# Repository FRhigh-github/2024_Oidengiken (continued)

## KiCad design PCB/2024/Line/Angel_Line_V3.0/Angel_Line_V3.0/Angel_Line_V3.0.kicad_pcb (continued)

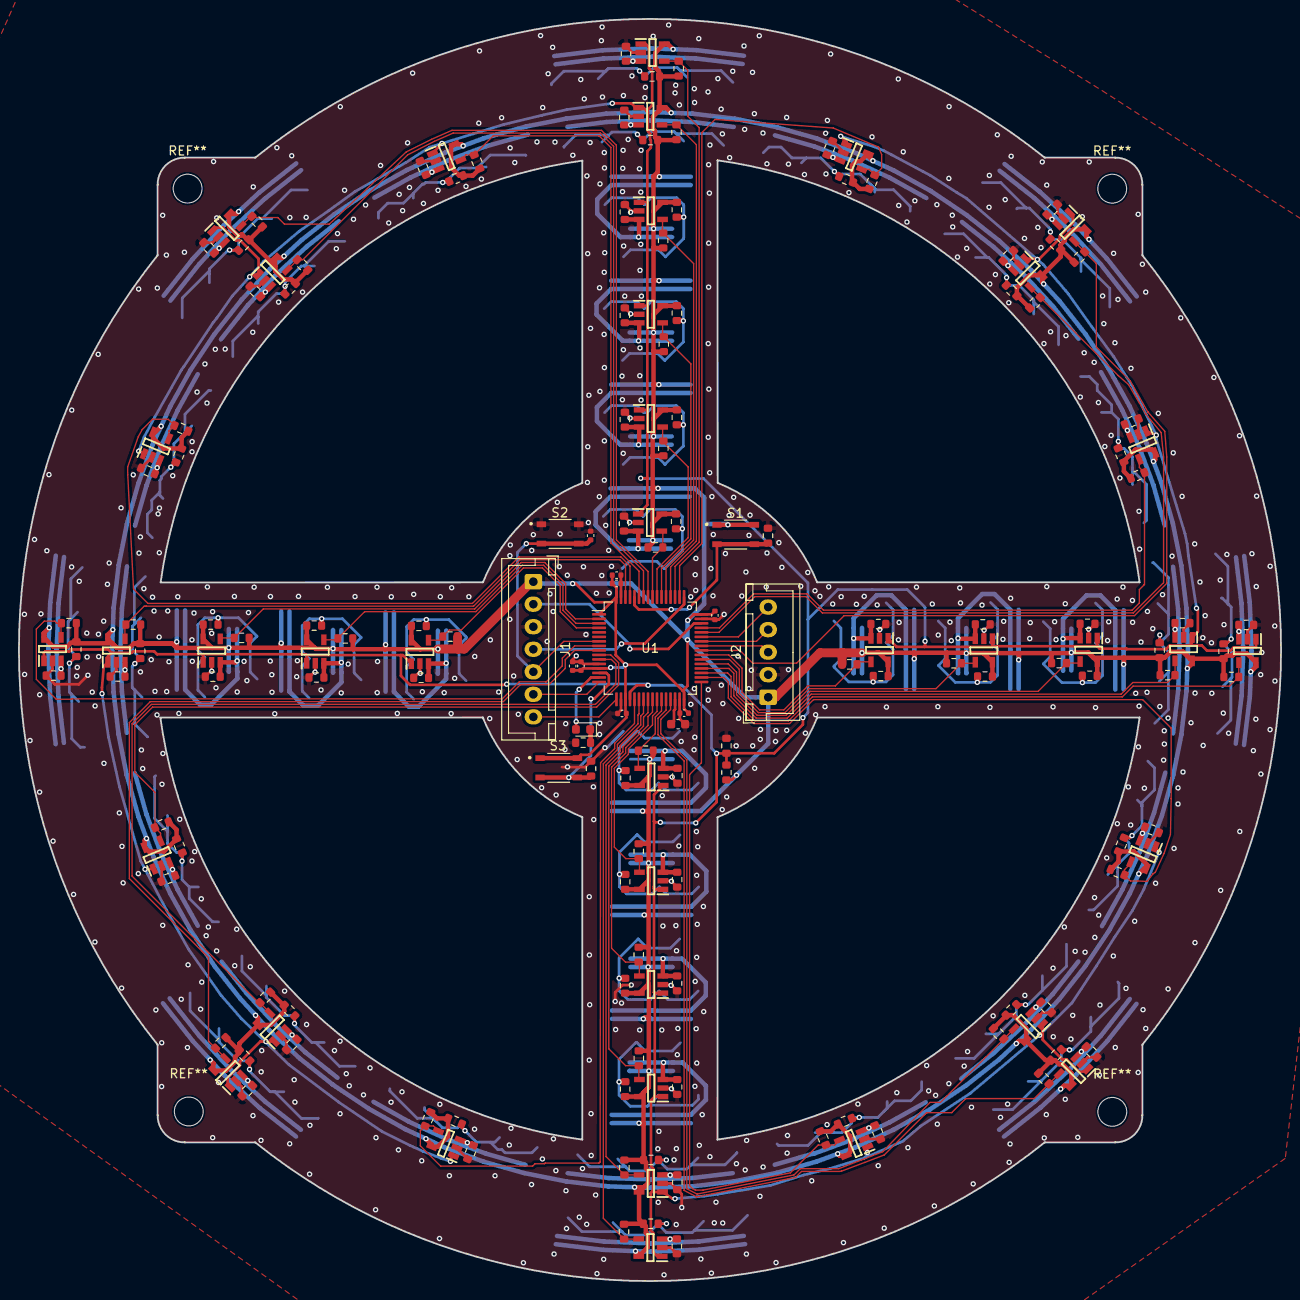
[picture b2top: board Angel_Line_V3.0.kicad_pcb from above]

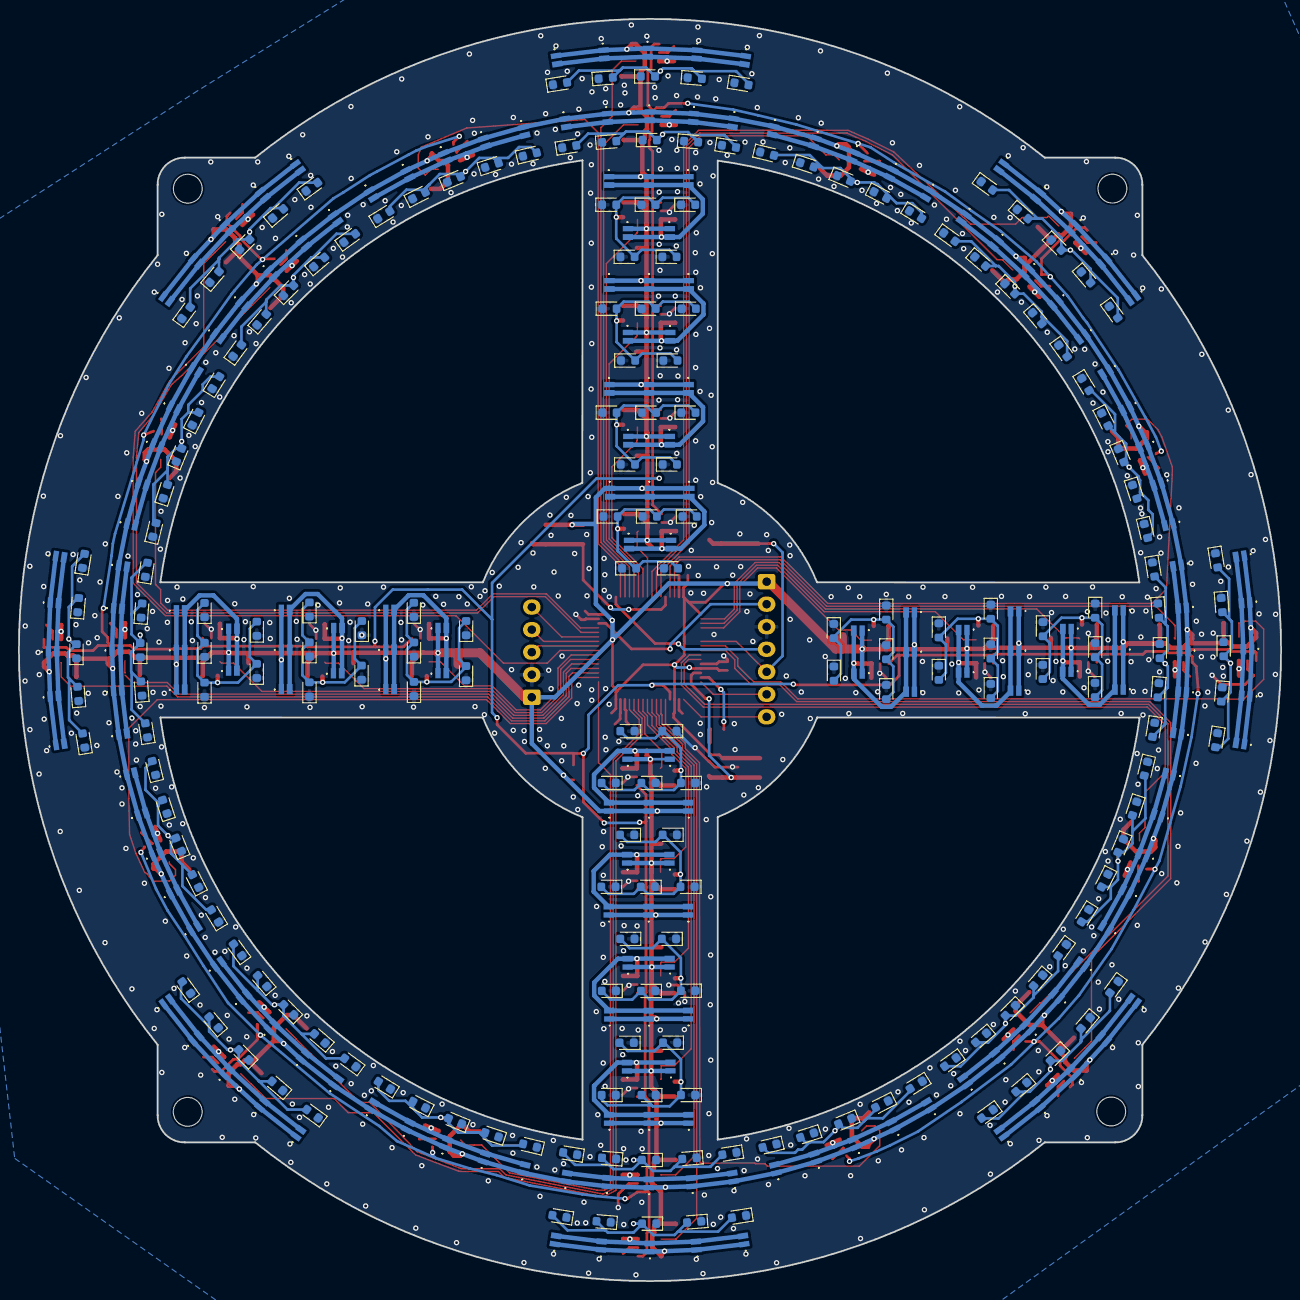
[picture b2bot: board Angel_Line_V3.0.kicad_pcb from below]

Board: 2 copper layers, 140.0 x 140.0 mm, 553 parts (380 on the bottom side), 130 nets.

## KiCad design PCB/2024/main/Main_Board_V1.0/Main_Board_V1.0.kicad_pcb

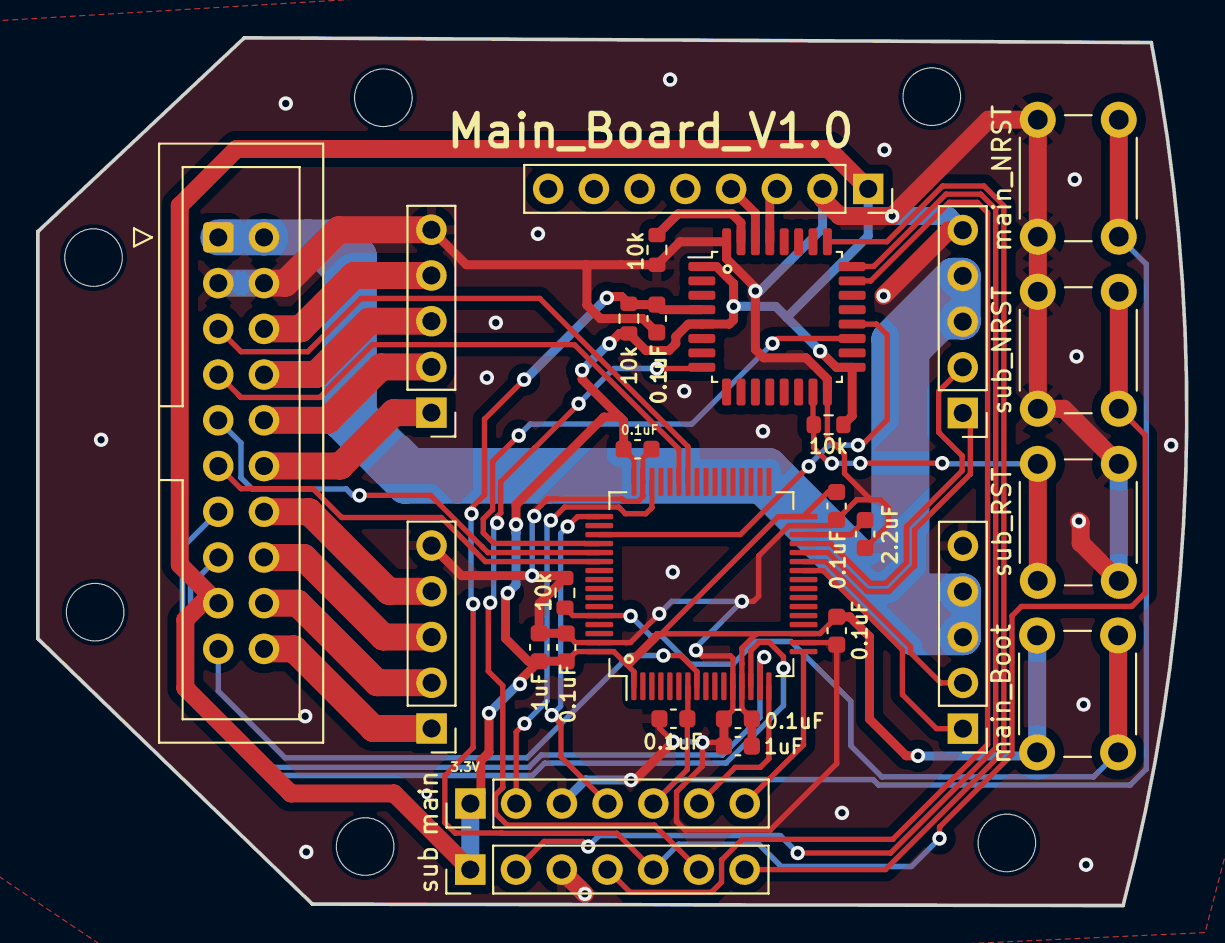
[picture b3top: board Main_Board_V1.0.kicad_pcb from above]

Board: 2 copper layers, 63.8 x 48.2 mm, 28 parts (0 on the bottom side), 40 nets.

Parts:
C1, C2, C3, C5, C7, C9, C10: 0.1uF; C_0603_1608Metric
C4: 2.2uF; C_0603_1608Metric
C6, C8: 1uF; C_0603_1608Metric
J1: Conn_01x08_Male; PinSocket_1x08_P2.54mm_Vertical
J3: Conn_02x10_Odd_Even; IDC-Header_2x10_P2.54mm_Vertical
J4, J5, J6, J7: Conn_01x05_Pin; PinHeader_1x05_P2.54mm_Vertical
R1, R2, R3, R4: 10k; R_0603_1608Metric
U1: STM32F446RETx; LQFP-64_10x10mm_P0.5mm
U2: STM32F303K8Tx; LQFP-32_7x7mm_P0.8mm
main: Conn_01x07_Female; PinHeader_1x07_P2.54mm_Vertical
main_Boot: SW_Push; SW_PUSH_6mm
main_NRST: SW_Push; SW_PUSH_6mm
sub: Conn_01x07_Female; PinHeader_1x07_P2.54mm_Vertical
sub_NRST: SW_Push; SW_PUSH_6mm
sub_RST: SW_Push; SW_PUSH_6mm

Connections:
+12V: J3.1, J3.2, J6.3, J6.4, J7.3, J7.4
MPU_SCL: J1.3, U2.29 (PB6)
MPU_SDA: J1.4, U2.30 (PB7)
Motor1_A: J3.20, J4.1
Motor1_B: J3.18, J4.2
Motor1_PWM: J6.1, U1.26 (PB0)
Motor2_A: J3.16, J4.3
Motor2_B: J3.14, J4.4
Motor2_PWM: J6.2, U1.27 (PB1)
Motor3_A: J3.12, J5.1
Motor3_B: J3.10, J5.2
Motor3_PWM: J7.1, U1.28 (PB2)
Motor4_A: J3.8, J5.3
Motor4_B: J3.6, J5.4
Motor4_PWM: J7.2, U1.29 (PB10)
unnamed: R3.2, U2.31 (BOOT0)
PC_RX: U2.25 (PA15), sub.7
PC_TX: U2.8 (PA2), sub.6
ST_SW: J3.19, U1.8 (PC0)
UART4_RX_OpenMV: J3.15, U1.15 (PA1)
UART4_TX_OpenMV: J3.13, U1.14 (PA0)
UART5_RX_Angel: J3.11, U1.54 (PD2)
UART5_TX_Angel: J3.9, U1.53 (PC12)
USART1_RX_IR: J3.7, U1.43 (PA10)
USART1_TX_IR: J3.5, U1.42 (PA9)
USART2_RX_USB: U1.17 (PA3), main.7
USART2_TX_USB: U1.16 (PA2), main.6
USART3_RX_IMU: U1.52 (PC11), U2.19 (PA9)
USART3_TX_IMU: U1.51 (PC10), U2.20 (PA10)
VCAP: C4.1, U1.30 (VCAP_1)
VDD1: C2.1, C3.1, C5.1, C6.1, C7.1, C8.1, C9.1, J1.1, J3.17, R1.1, R2.2, U1.1 (VBAT), U1.13 (VDDA), U1.19 (VDD), U1.32 (VDD), U1.48 (VDD), U1.64 (VDD), U2.1 (VDD), U2.5 (VDDA), U2.17 (VDD), main.1, main_Boot.1, sub.1
VSSA: C1.2, C2.2, C3.2, C4.2, C5.2, C6.2, C7.2, C8.2, C9.2, C10.2, J1.2, J3.3, J3.4, J4.5, J5.5, J6.5, J7.5, R3.1, R4.2, U1.12 (VSSA), U1.18 (VSS), U1.31 (VSS), U1.47 (VSS), U1.63 (VSS), U2.16 (VSS), U2.32 (VSS), main.3, main_NRST.1, sub.3, sub_NRST.1, sub_RST.2
main_BOOT: R4.1, U1.60 (BOOT0), main_Boot.2
main_NRST: C10.1, U1.7 (NRST), main.5, main_NRST.2
main_SWCLK: U1.46 (PA13), main.2
main_SWDIO: U1.49 (PA14), main.4
sub_NRST: C1.1, R2.1, U2.4 (NRST), sub.5, sub_NRST.2
sub_RST: R1.2, U2.15 (PB1), sub_RST.1
sub_SWCLK: U2.24 (PA14), sub.2
sub_SWDIO: U2.23 (PA13), sub.4

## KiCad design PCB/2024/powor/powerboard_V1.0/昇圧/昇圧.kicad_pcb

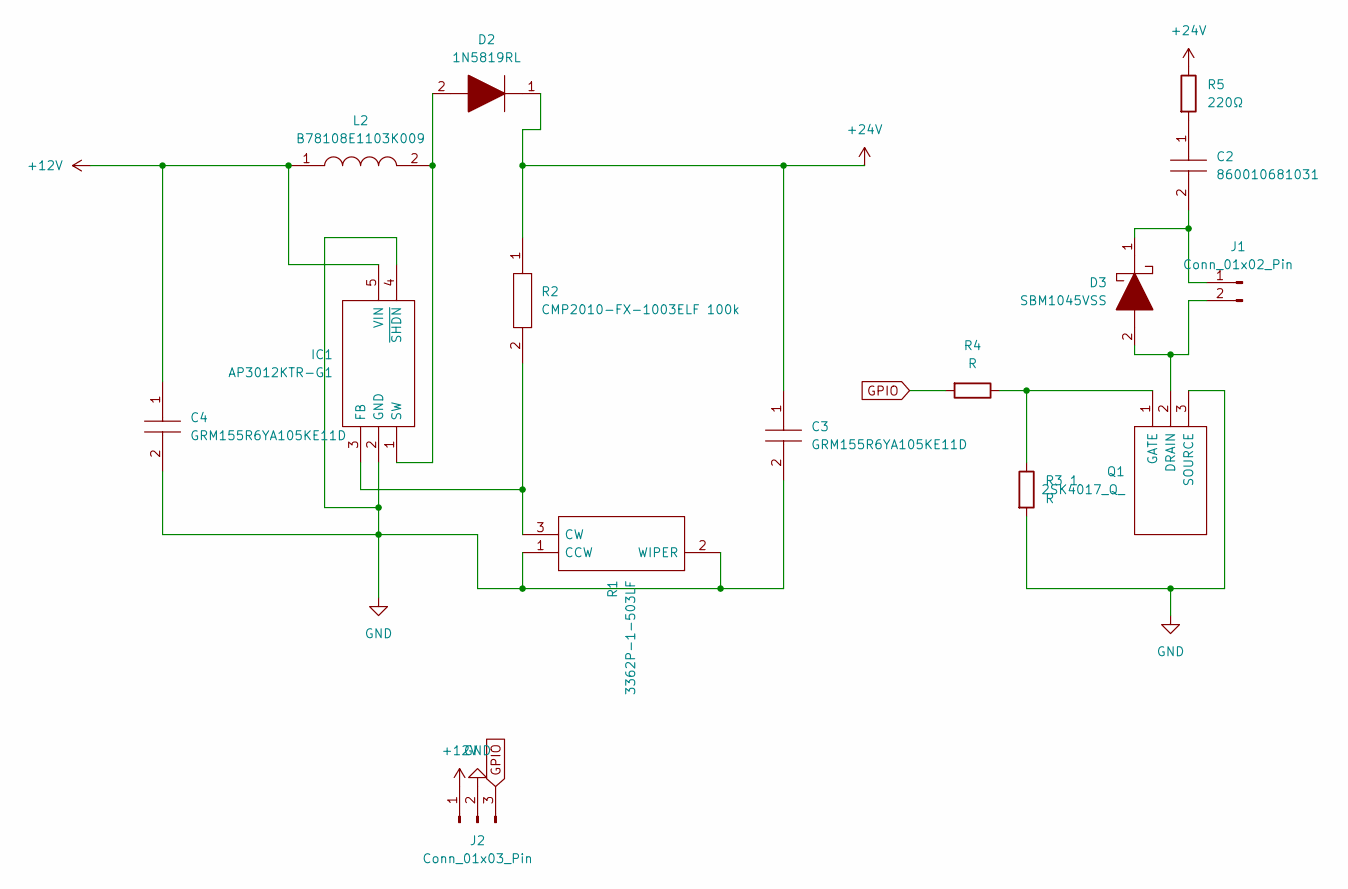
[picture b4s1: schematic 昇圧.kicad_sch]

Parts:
C2: 860010681031; CAPPRD750W82D1800H4300; Manufacturer_Part_Number 860010681031
C3, C4: GRM155R6YA105KE11D; CAPC1005X55N; Manufacturer_Part_Number GRM155R6YA105KE11D
D2: 1N5819RL; DIOAD1414W86L464D238; Manufacturer_Part_Number 1N5819RL
D3: SBM1045VSS; DIOAD2855W130L835D505; Manufacturer_Part_Number SBM1045VSS
IC1: AP3012KTR-G1; SOT95P280X145-5N; Manufacturer_Part_Number AP3012KTR-G1
J1: Conn_01x02_Pin; JST_XH_B2B-XH-AM_1x02_P2.50mm_Vertical
J2: Conn_01x03_Pin; JST_XH_B3B-XH-AM_1x03_P2.50mm_Vertical
L2: B78108E1103K009; B78108E; Manufacturer_Part_Number B78108E1103K009
Q1: 2SK4017_Q_; TO230P250X650X900-3P; Manufacturer_Part_Number 2SK4017(Q)
R1: 3362P-1-503LF; 3362P_1; Manufacturer_Part_Number 3362P-1-503LF
R2: CMP2010-FX-1003ELF 100k; RESC5025X70N; Manufacturer_Part_Number CMP2010-FX-1003ELF
R3　1, R4: R; R_0603_1608Metric_Pad0.98x0.95mm_HandSolder
R5: 220Ω; R_Axial_DIN0516_L15.5mm_D5.0mm_P25.40mm_Horizontal

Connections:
+12V: C4.1, IC1.5 (VIN), J2.1, L2.1
+24V: C3.1, D2.1, R2.1, R5.1
GND: C3.2, C4.2, IC1.2 (GND), IC1.4 (~SHDN), J2.2, Q1.3 (SOURCE), R1.1 (CCW), R1.2 (WIPER), R3 1.2
GPIO: J2.3, R4.2
unnamed: C2.1, R5.2
unnamed: IC1.3 (FB), R1.3 (CW), R2.2
unnamed: D2.2, IC1.1 (SW), L2.2
unnamed: C2.2, D3.1, J1.1
unnamed: D3.2, J1.2, Q1.2 (DRAIN)
unnamed: Q1.1 (GATE), R3 1.1, R4.1

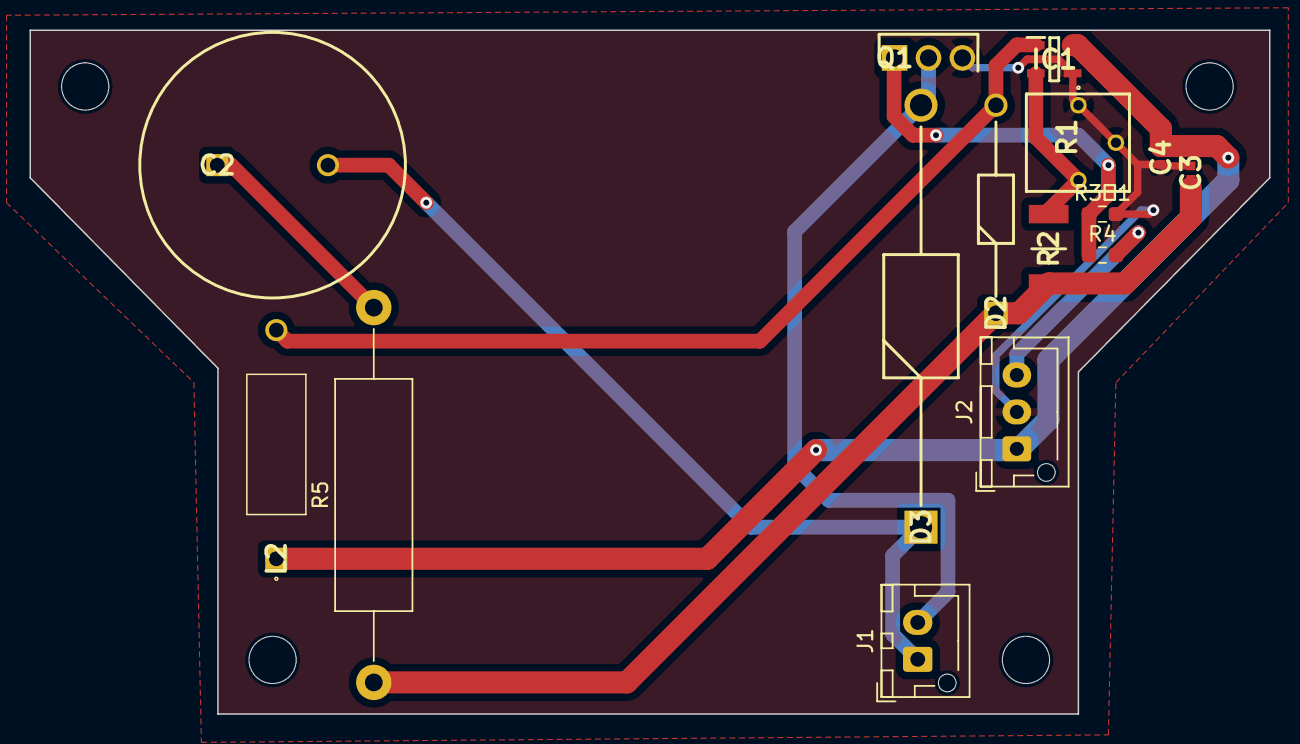
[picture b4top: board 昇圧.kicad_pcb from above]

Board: 2 copper layers, 84.0 x 46.3 mm, 15 parts (0 on the bottom side), 10 nets.

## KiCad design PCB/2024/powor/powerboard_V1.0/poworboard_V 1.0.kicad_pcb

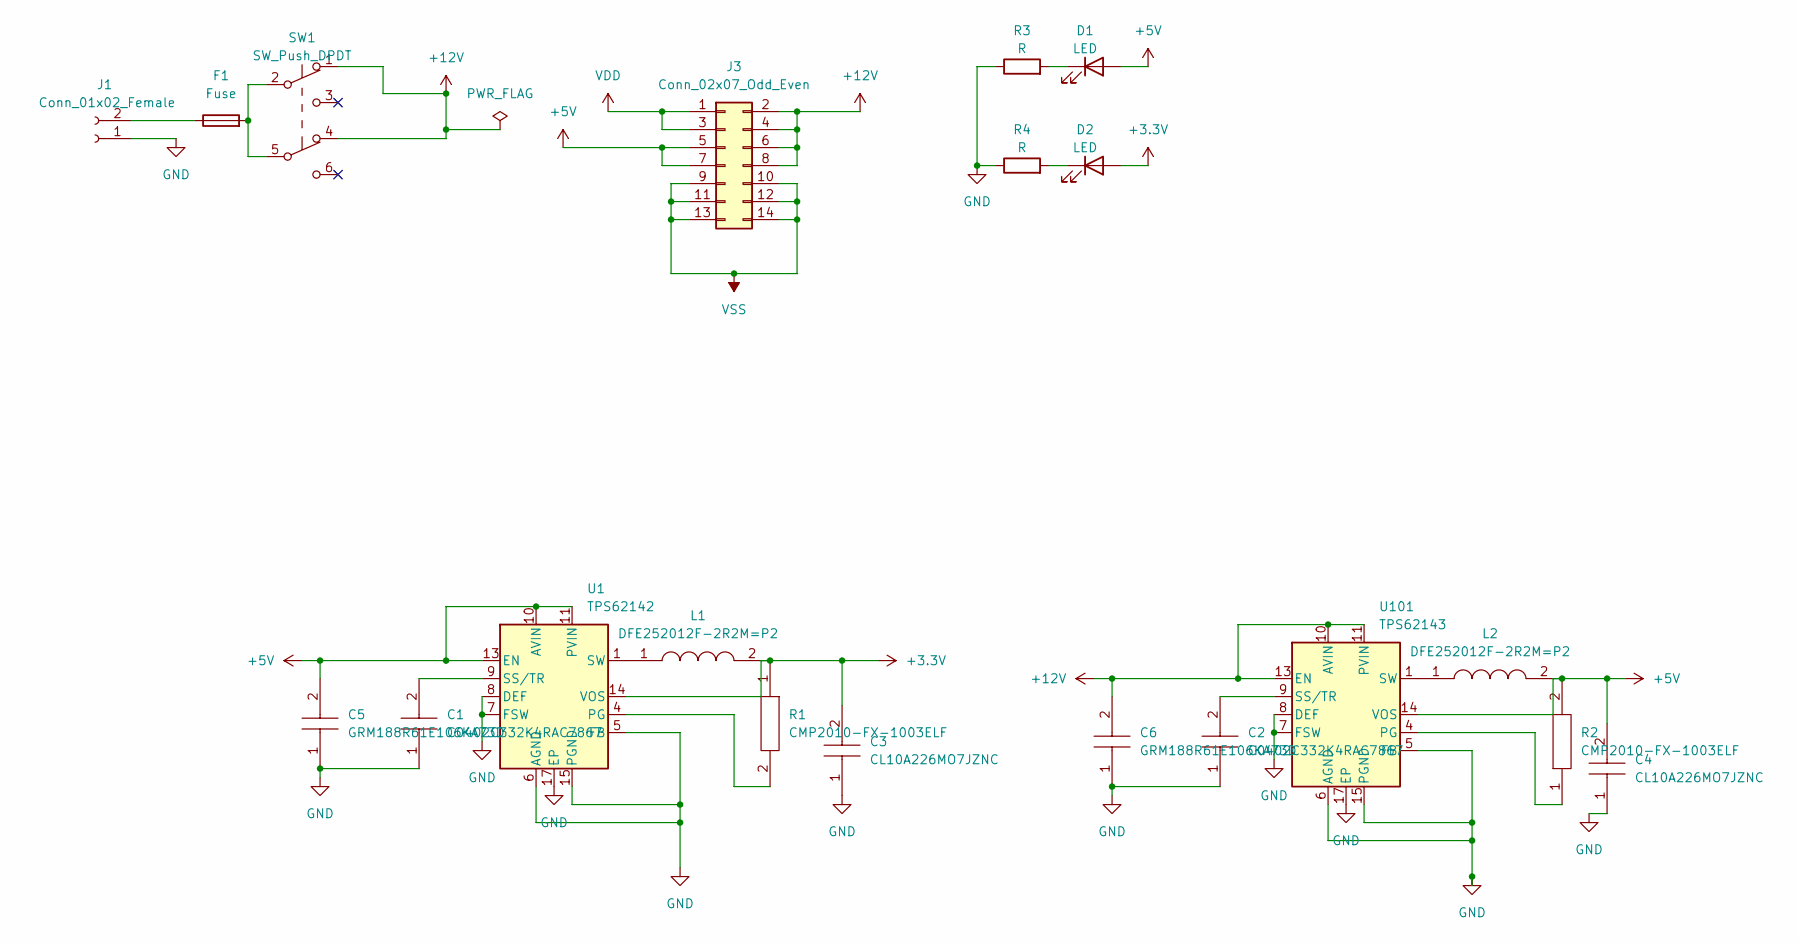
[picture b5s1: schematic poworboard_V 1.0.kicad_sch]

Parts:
C1, C2: C0402C332K4RAC7867; C0402; Manufacturer_Part_Number C0402C332K4RAC7867
C3, C4: CL10A226MO7JZNC; CAPC1608X80N; Manufacturer_Part_Number CL10A226MO7JZNC
C5, C6: GRM188R61E106KA73D; CAPC1608X90N; Manufacturer_Part_Number GRM188R61E106KA73D
D1, D2: LED; LED_0603_1608Metric
F1: Fuse; Fuseholder_Cylinder-5x20mm_Schurter_0031_8201_Horizontal_Op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
J1: Conn_01x02_Female; TerminalBlock_bornier-2_P5.08mm
J3: Conn_02x07_Odd_Even; IDC-Header_2x07_P2.54mm_Vertical
L1, L2: DFE252012F-2R2M=P2; DFE2HCAH1R0MJ0L; Manufacturer_Part_Number DFE252012F-2R2M=P2
R1, R2: CMP2010-FX-1003ELF; RESC5025X70N; Manufacturer_Part_Number CMP2010-FX-1003ELF
R3, R4: R; R_0603_1608Metric
SW1: SW_Push_DPDT; Toggle
U1: TPS62142; VQFN-16-1EP_3x3mm_P0.5mm_EP1.68x1.68mm_ThermalVias
U101: TPS62143; VQFN-16-1EP_3x3mm_P0.5mm_EP1.68x1.68mm_ThermalVias

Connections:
+3.3V: C3.2, D2.2 (A), L1.2, R1.1, U1.14 (VOS)
+5V: C4.2, C5.2, D1.2 (A), J3.5, J3.7, L2.2, R2.2, U1.10 (AVIN), U1.11 (PVIN), U1.12 (PVIN), U1.13 (EN), U101.14 (VOS); also elsewhere on the board
+12V: C6.2, J3.2, J3.4, J3.6, J3.8, SW1.1 (A), SW1.4 (A), U101.10 (AVIN), U101.11 (PVIN), U101.12 (PVIN), U101.13 (EN)
GND: C1.1, C2.1, C3.1, C4.1, C5.1, C6.1, J1.1, R3.1, R4.1, U1.5 (FB), U1.6 (AGND), U1.7 (FSW), U1.8 (DEF), U1.15 (PGND), U1.16 (PGND), U1.17 (EP), U101.5 (FB), U101.6 (AGND), U101.7 (FSW), U101.8 (DEF), U101.15 (PGND), U101.16 (PGND), U101.17 (EP)
unnamed: D1.1 (K), R3.2
unnamed: D2.1 (K), R4.2
unnamed: F1.2, SW1.2 (B), SW1.5 (B)
unnamed: F1.1, J1.2
unnamed: L1.1, U1.1 (SW), U1.2 (SW), U1.3 (SW)
unnamed: L2.1, U101.1 (SW), U101.2 (SW), U101.3 (SW)
unnamed: R1.2, U1.4 (PG)
unnamed: C1.2, U1.9 (SS/TR)
unnamed 12: R2.1, U101.4 (PG); also elsewhere on the board
unnamed: C2.2, U101.9 (SS/TR)
VDD: J3.1, J3.3
VSS: J3.9, J3.10, J3.11, J3.12, J3.13, J3.14

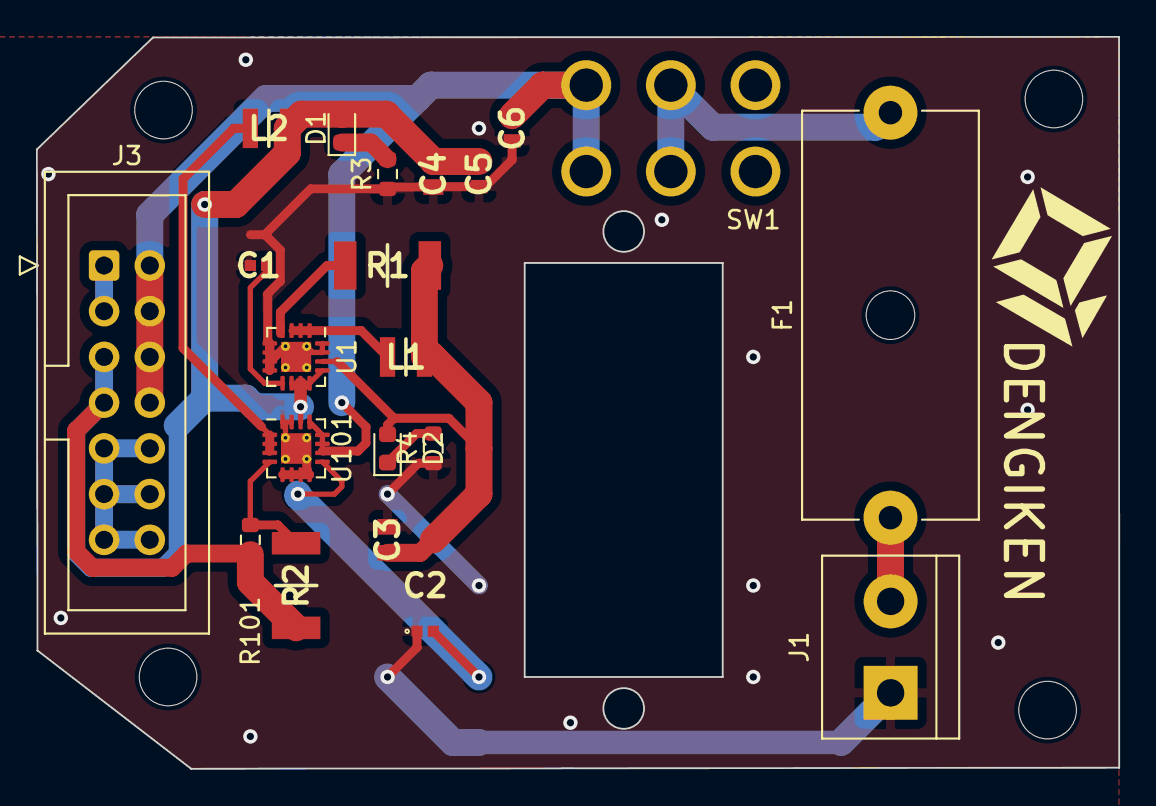
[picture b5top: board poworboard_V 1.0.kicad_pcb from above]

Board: 2 copper layers, 60.1 x 40.7 mm, 21 parts (0 on the bottom side), 16 nets.

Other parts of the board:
R101: 100k; R_0603_1608Metric

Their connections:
+5V: R101.1; also elsewhere on the board
unnamed 12: R101.2; also elsewhere on the board

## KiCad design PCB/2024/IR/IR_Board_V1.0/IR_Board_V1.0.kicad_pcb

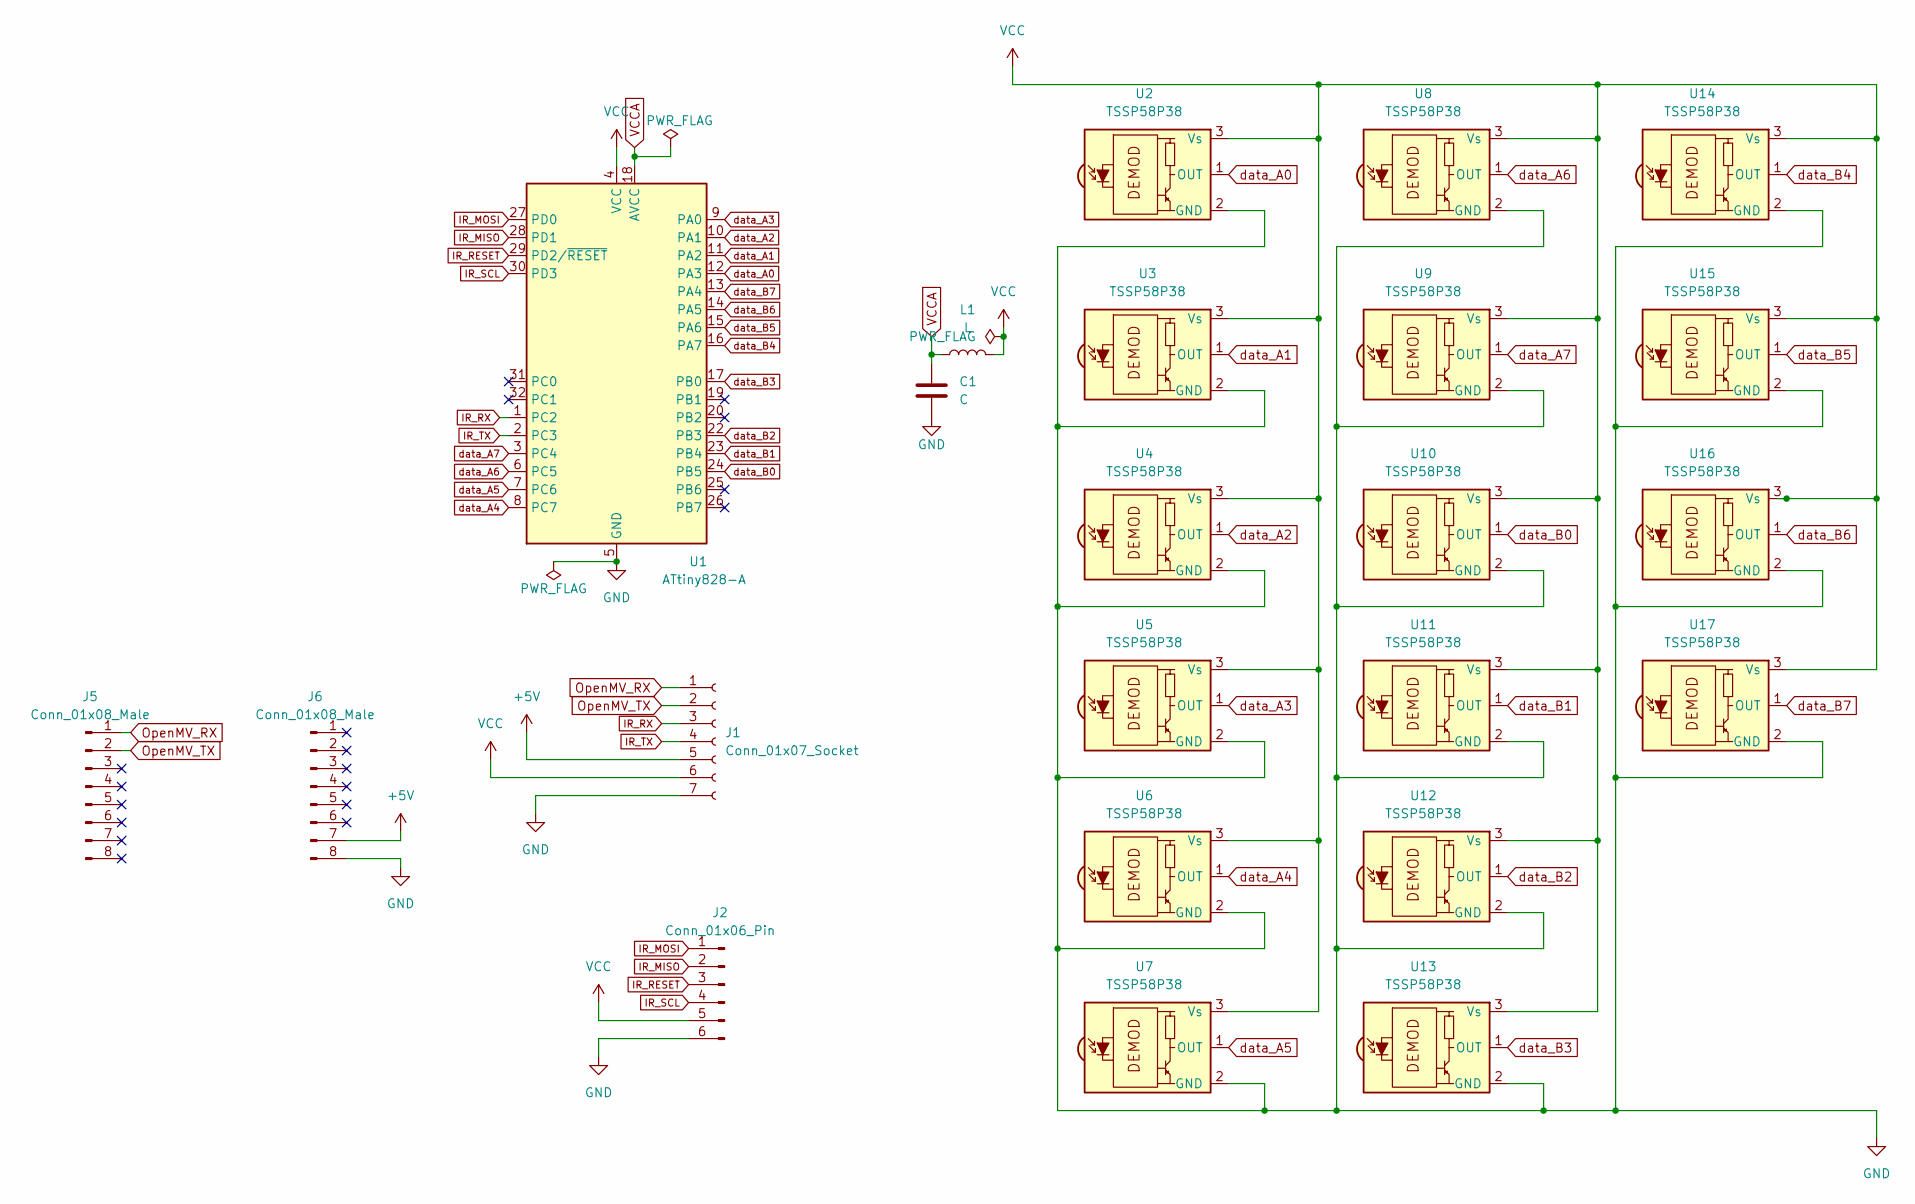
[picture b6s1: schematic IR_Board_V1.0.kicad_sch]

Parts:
C1: C; C_0603_1608Metric
J1: Conn_01x07_Socket; JST_XH_B7B-XH-A_1x07_P2.50mm_Vertical
J2: Conn_01x06_Pin; PinHeader_1x06_P2.54mm_Horizontal
J5, J6: Conn_01x08_Male; PinHeader_1x08_P2.54mm_Vertical
L1: L; L_Axial_L6.6mm_D2.7mm_P10.16mm_Horizontal_Vishay_IM-2
U1: ATtiny828-A; TQFP-32_7x7mm_P0.8mm
U2, U3, U4, U5, U6, U7, U8, U9, U10, U11, U12, U13, U14, U15, U16, U17: TSSP58P38; Vishay_MINICAST-3Pin

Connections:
+5V: J1.5; also elsewhere on the board
GND: C1.2, J1.7, J2.6, U1.5 (GND), U1.21 (GND), U2.2 (GND), U3.2 (GND), U4.2 (GND), U5.2 (GND), U6.2 (GND), U7.2 (GND), U8.2 (GND), U9.2 (GND), U10.2 (GND), U11.2 (GND), U12.2 (GND), U13.2 (GND), U14.2 (GND), U15.2 (GND), U16.2 (GND), U17.2 (GND); also elsewhere on the board
IR_MISO: J2.2, U1.28 (PD1)
IR_MOSI: J2.1, U1.27 (PD0)
IR_RESET: J2.3, U1.29 (PD2/~RESET)
IR_RX: J1.3, U1.1 (PC2)
IR_SCL: J2.4, U1.30 (PD3)
IR_TX: J1.4, U1.2 (PC3)
OpenMV_RX: J1.1; also elsewhere on the board
OpenMV_TX: J1.2; also elsewhere on the board
VCC: J1.6, J2.5, L1.2, U1.4 (VCC), U2.3 (Vs), U3.3 (Vs), U4.3 (Vs), U5.3 (Vs), U6.3 (Vs), U7.3 (Vs), U8.3 (Vs), U9.3 (Vs), U10.3 (Vs), U11.3 (Vs), U12.3 (Vs), U13.3 (Vs), U14.3 (Vs), U15.3 (Vs), U16.3 (Vs), U17.3 (Vs)
VCCA: C1.1, L1.1, U1.18 (AVCC)
data_A0: U1.12 (PA3), U2.1 (OUT)
data_A1: U1.11 (PA2), U3.1 (OUT)
data_A2: U1.10 (PA1), U4.1 (OUT)
data_A3: U1.9 (PA0), U5.1 (OUT)
data_A4: U1.8 (PC7), U6.1 (OUT)
data_A5: U1.7 (PC6), U7.1 (OUT)
data_A6: U1.6 (PC5), U8.1 (OUT)
data_A7: U1.3 (PC4), U9.1 (OUT)
data_B0: U1.24 (PB5), U10.1 (OUT)
data_B1: U1.23 (PB4), U11.1 (OUT)
data_B2: U1.22 (PB3), U12.1 (OUT)
data_B3: U1.17 (PB0), U13.1 (OUT)
data_B4: U1.16 (PA7), U14.1 (OUT)
data_B5: U1.15 (PA6), U15.1 (OUT)
data_B6: U1.14 (PA5), U16.1 (OUT)
data_B7: U1.13 (PA4), U17.1 (OUT)

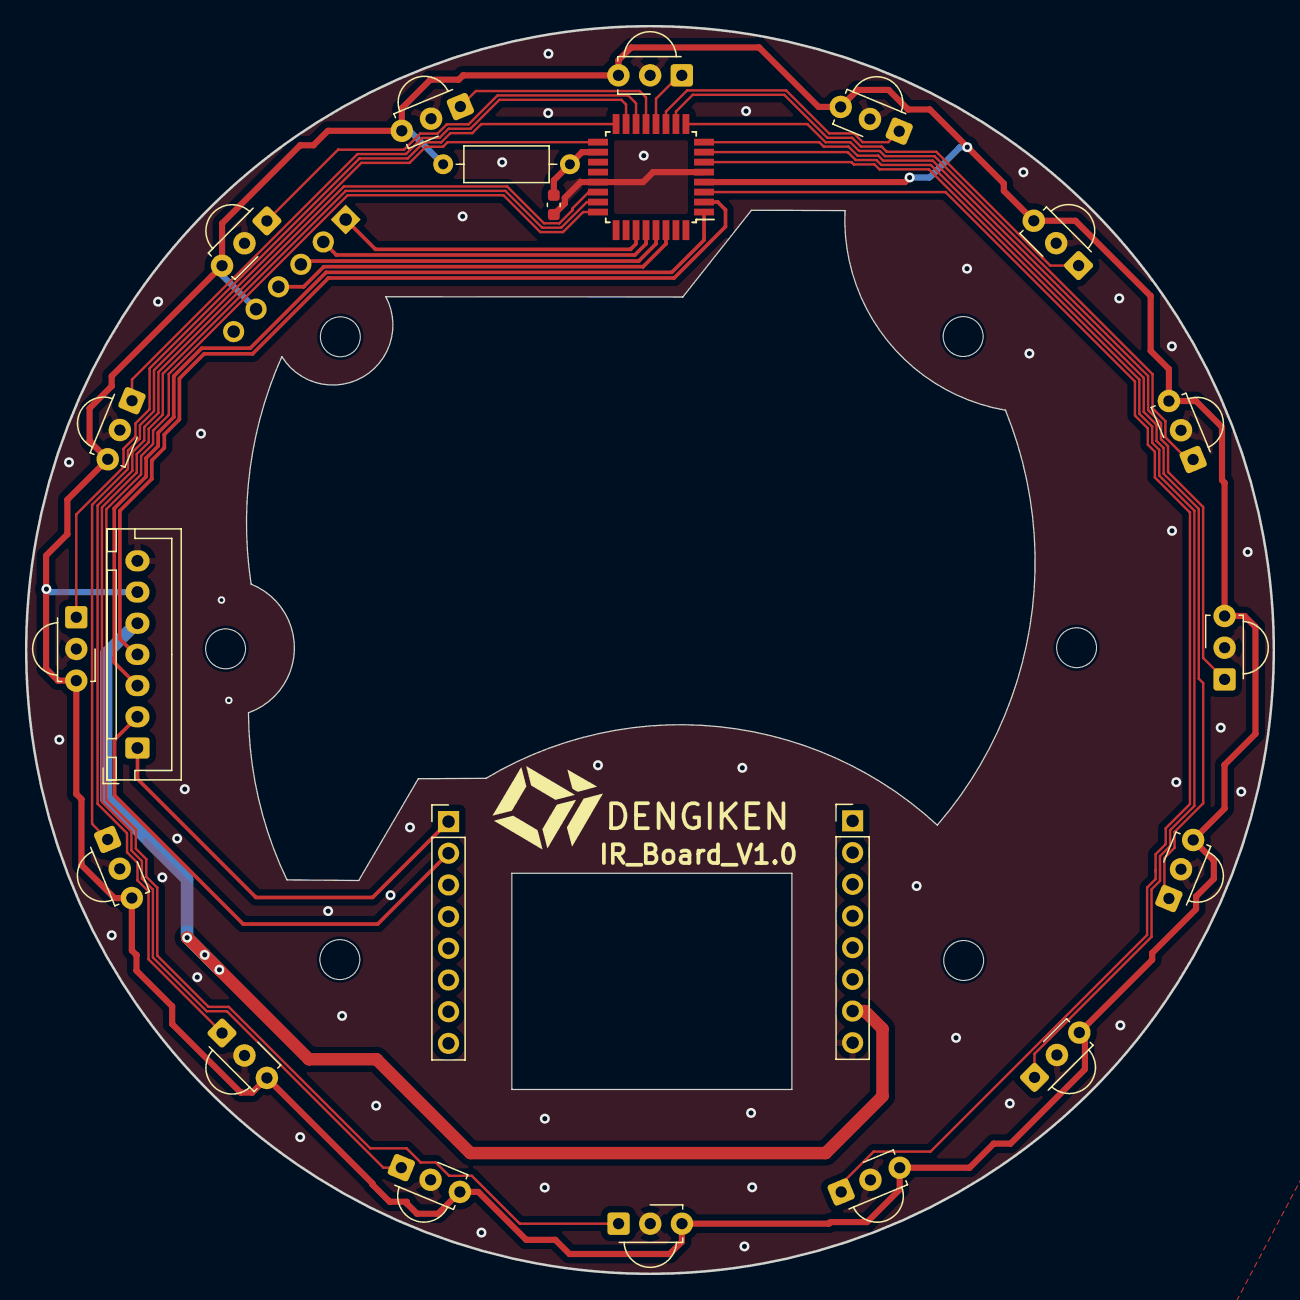
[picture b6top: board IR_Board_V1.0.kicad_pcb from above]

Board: 2 copper layers, 100.0 x 100.0 mm, 23 parts (1 on the bottom side), 28 nets.

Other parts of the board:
J3, J4: Conn_01x08_Male; PinHeader_1x08_P2.54mm_Vertical

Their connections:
+5V: J4.7; also elsewhere on the board
GND: J4.8; also elsewhere on the board
OpenMV_RX: J3.1; also elsewhere on the board
OpenMV_TX: J3.2; also elsewhere on the board
